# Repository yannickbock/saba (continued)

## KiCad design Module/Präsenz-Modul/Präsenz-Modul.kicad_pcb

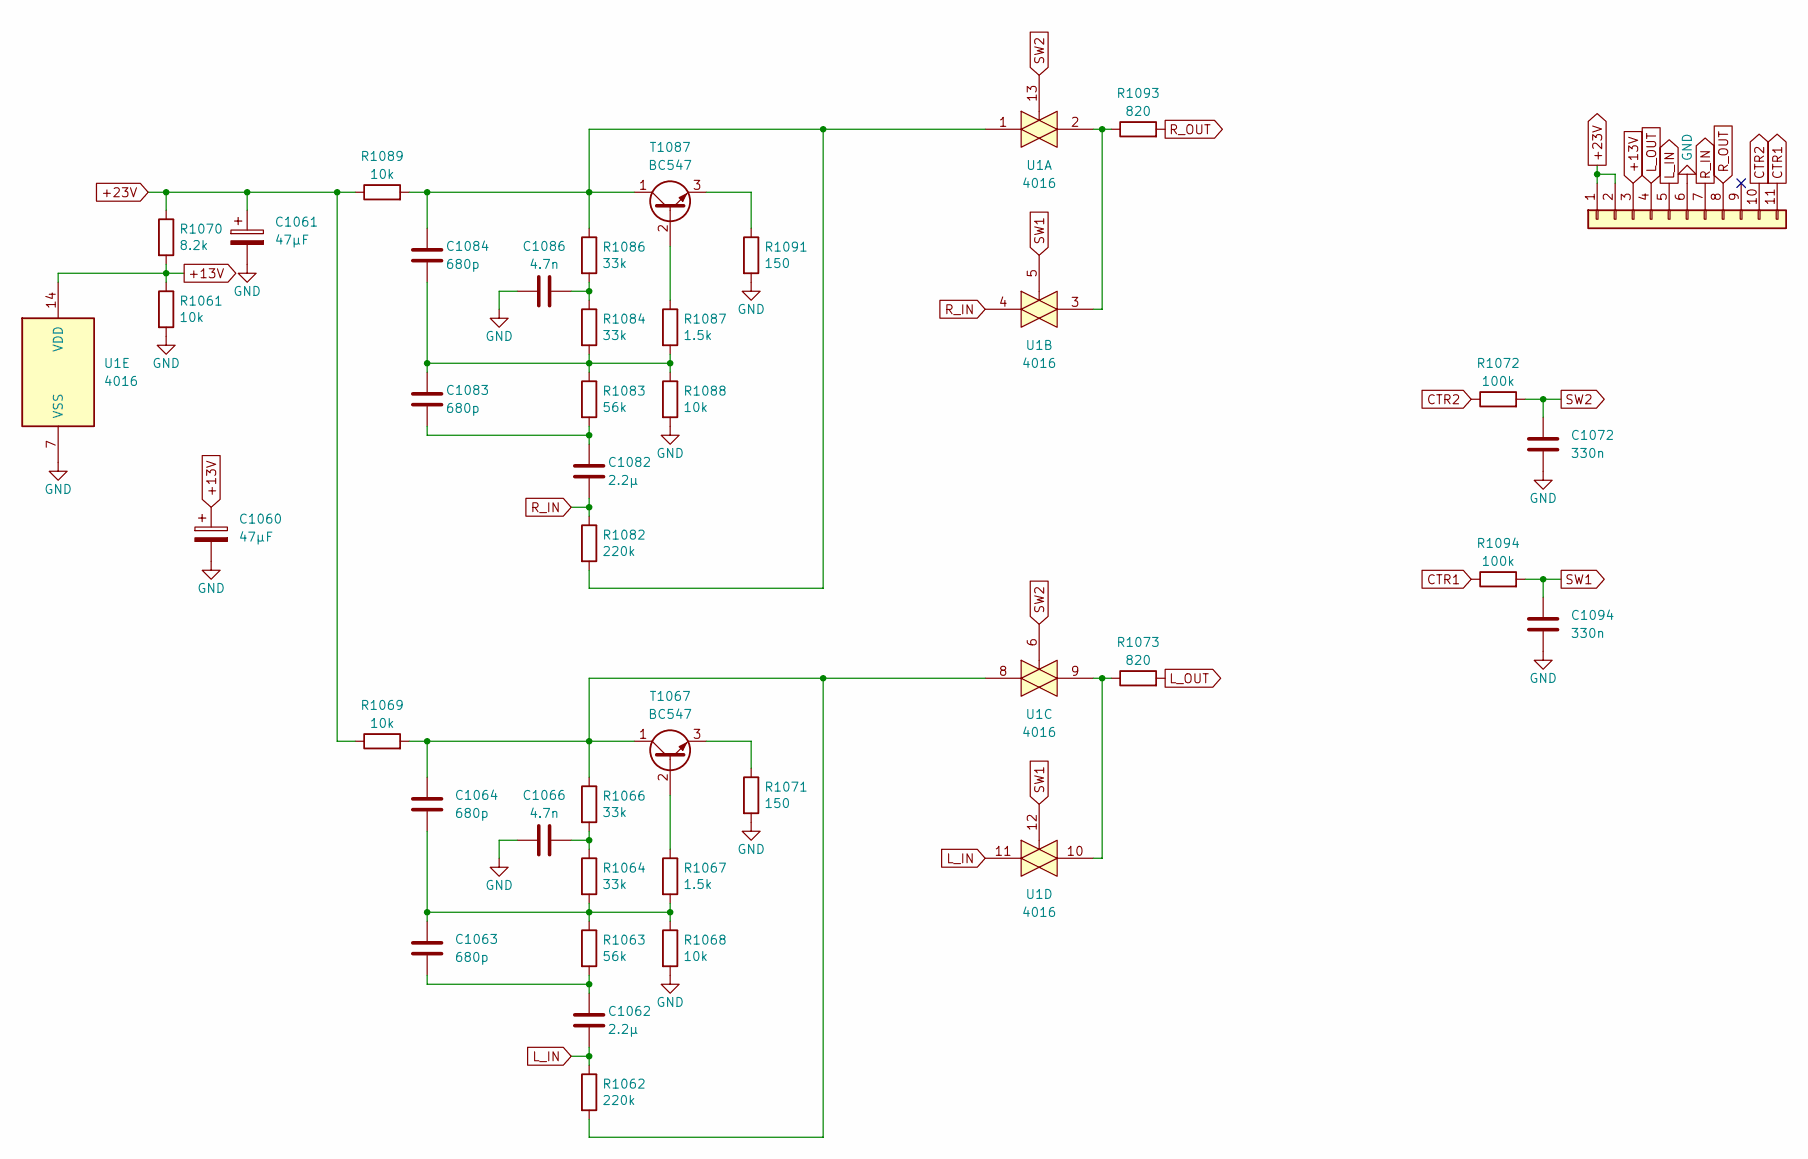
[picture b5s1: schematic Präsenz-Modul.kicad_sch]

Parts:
C1060, C1061: 47µF; CP_Radial_D6.3mm_P2.50mm
C1062, C1082: 2.2µ; C_Rect_L7.2mm_W7.2mm_P5.00mm_FKS2_FKP2_MKS2_MKP2
C1063, C1083: 680p; C_Rect_L10.0mm_W3.0mm_P7.50mm_MKS4
C1064, C1084: 680p; C_RAD_6.5mm_5mm
C1066, C1086: 4.7n; C_Rect_L10.0mm_W3.0mm_P7.50mm_MKS4
C1072, C1094: 330n; C_Rect_L7.2mm_W3.5mm_P5.00mm_FKS2_FKP2_MKS2_MKP2
J1: Conn_01x13; Connector_01x11_5mm
R1061, R1068, R1069, R1088, R1089: 10k; R_Axial_DIN0207_L6.3mm_D2.5mm_P10.16mm_Horizontal
R1062, R1082: 220k; R_Axial_DIN0207_L6.3mm_D2.5mm_P10.16mm_Horizontal
R1063, R1083: 56k; R_Axial_DIN0207_L6.3mm_D2.5mm_P10.16mm_Horizontal
R1064, R1066, R1084, R1086: 33k; R_Axial_DIN0207_L6.3mm_D2.5mm_P10.16mm_Horizontal
R1067, R1087: 1.5k; R_Axial_DIN0207_L6.3mm_D2.5mm_P10.16mm_Horizontal
R1070: 8.2k; R_Axial_DIN0207_L6.3mm_D2.5mm_P10.16mm_Horizontal
R1071, R1091: 150; R_Axial_DIN0207_L6.3mm_D2.5mm_P10.16mm_Horizontal
R1072, R1094: 100k; R_Axial_DIN0207_L6.3mm_D2.5mm_P10.16mm_Horizontal
R1073, R1093: 820; R_Axial_DIN0207_L6.3mm_D2.5mm_P10.16mm_Horizontal
T1067, T1087: BC547; TO-92_Wide
U1: 4016; DIP-14_W7.62mm

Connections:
+13V: C1060.1, J1.3, R1061.1, R1070.2, U1.14 (VDD)
+23V: C1061.1, J1.1, J1.2, R1069.1, R1070.1, R1089.1
CTR1: J1.11, R1094.1
CTR2: J1.10, R1072.1
GND: C1060.2, C1061.2, C1066.1, C1072.2, C1086.1, C1094.2, J1.6, R1061.2, R1068.2, R1071.2, R1088.2, R1091.2, U1.7 (VSS)
L_IN: C1062.2, J1.5, R1062.1, U1.11
L_OUT: J1.4, R1073.2
unnamed: C1062.1, C1063.2, R1063.2
unnamed: C1063.1, C1064.2, R1063.1, R1064.2, R1067.2, R1068.1
unnamed: C1066.2, R1064.1, R1066.2
unnamed: C1082.1, C1083.2, R1083.2
unnamed: C1083.1, C1084.2, R1083.1, R1084.2, R1087.2, R1088.1
unnamed: C1086.2, R1084.1, R1086.2
unnamed: R1073.1, U1.9, U1.10
unnamed: R1093.1, U1.2, U1.3
unnamed: R1067.1, T1067.2 (B)
unnamed: C1064.1, R1062.2, R1066.1, R1069.2, T1067.1 (C), U1.8
unnamed: R1071.1, T1067.3 (E)
unnamed: R1087.1, T1087.2 (B)
unnamed: C1084.1, R1082.2, R1086.1, R1089.2, T1087.1 (C), U1.1
unnamed: R1091.1, T1087.3 (E)
R_IN: C1082.2, J1.7, R1082.1, U1.4
R_OUT: J1.8, R1093.2
SW1: C1094.1, R1094.2, U1.5, U1.12
SW2: C1072.1, R1072.2, U1.6, U1.13

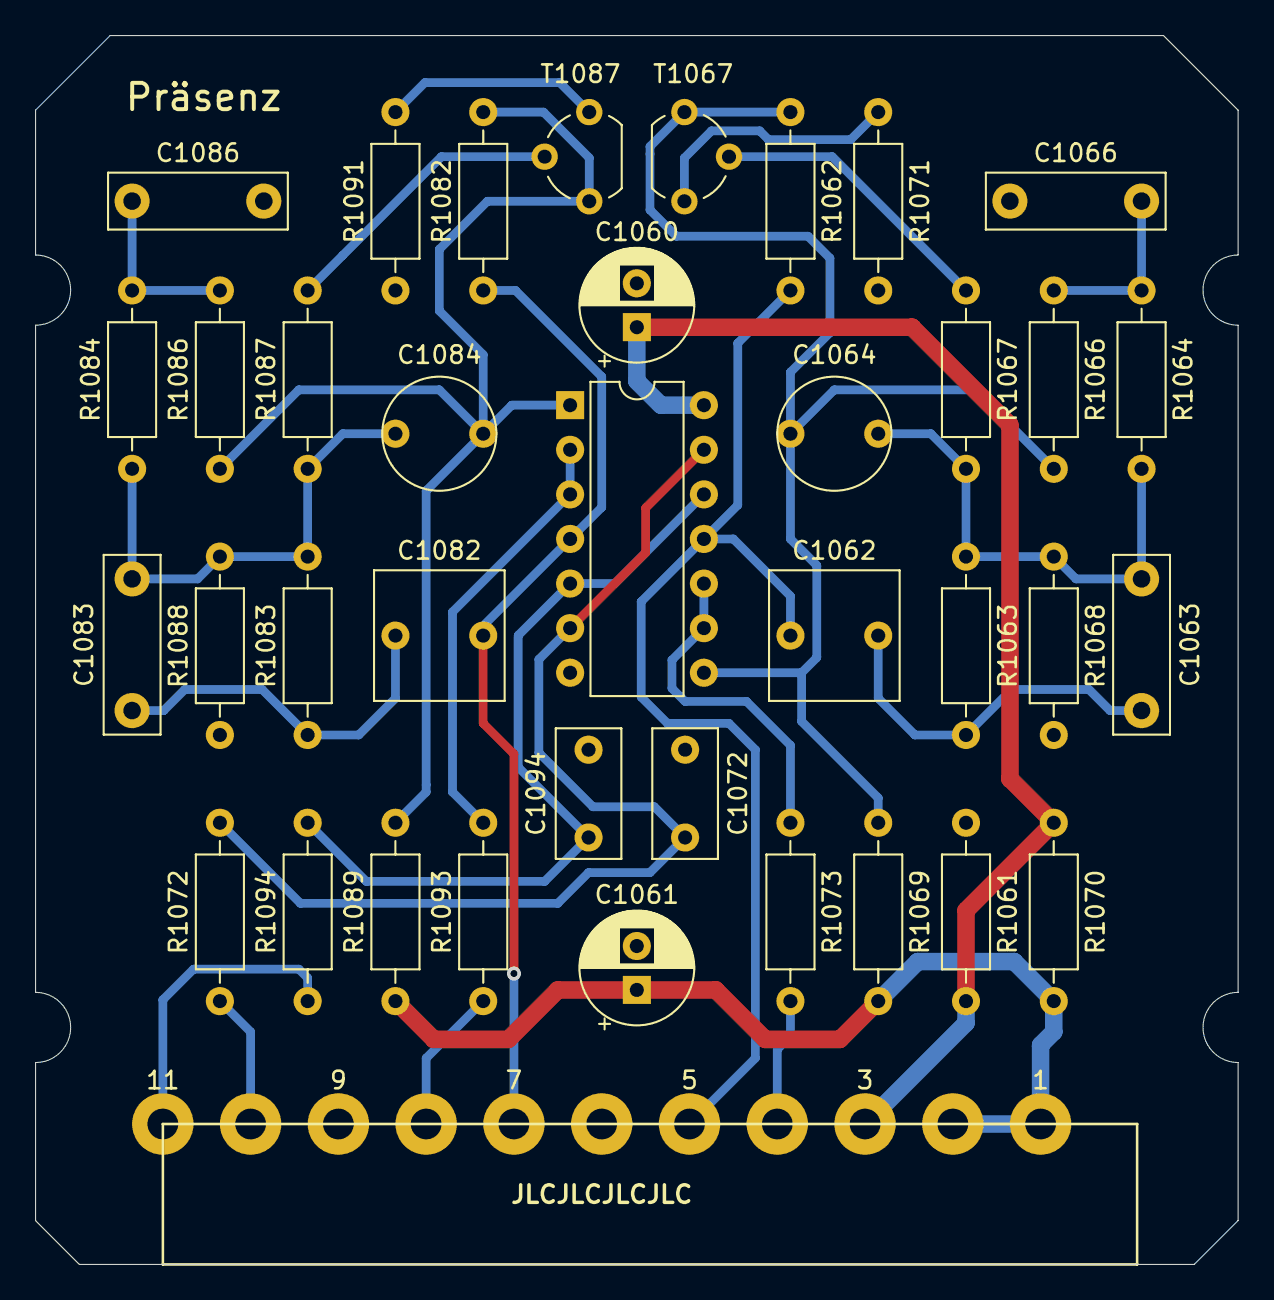
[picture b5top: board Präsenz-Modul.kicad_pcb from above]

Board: 2 copper layers, 68.5 x 70.0 mm, 38 parts (0 on the bottom side), 25 nets.

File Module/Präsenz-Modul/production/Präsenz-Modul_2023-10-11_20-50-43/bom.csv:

Designator,Footprint,Quantity,Value,LCSC Part #
"C1060, C1061",CP_Radial_D6.3mm_P2.50mm,2,47µF,
"C1062, C1082",C_Rect_L7.2mm_W7.2mm_P5.00mm_FKS2_FKP2_MKS2_MKP2,2,2.2µ,
"C1063, C1083",C_Rect_L10.0mm_W3.0mm_P7.50mm_MKS4,2,680p,
"C1064, C1084",C_RAD_6.5mm_5mm,2,680p,
"C1066, C1086",C_Rect_L10.0mm_W3.0mm_P7.50mm_MKS4,2,4.7n,
"C1072, C1094",C_Rect_L7.2mm_W3.5mm_P5.00mm_FKS2_FKP2_MKS2_MKP2,2,330n,
J1,Connector_01x11_5mm,1,Conn_01x13,
"R1061, R1068, R1069, R1088, R1089",R_Axial_DIN0207_L6.3mm_D2.5mm_P10.16mm_Horizontal,5,10k,
"R1062, R1082",R_Axial_DIN0207_L6.3mm_D2.5mm_P10.16mm_Horizontal,2,220k,
"R1063, R1083",R_Axial_DIN0207_L6.3mm_D2.5mm_P10.16mm_Horizontal,2,56k,
"R1064, R1066, R1084, R1086",R_Axial_DIN0207_L6.3mm_D2.5mm_P10.16mm_Horizontal,4,33k,
"R1067, R1087",R_Axial_DIN0207_L6.3mm_D2.5mm_P10.16mm_Horizontal,2,1.5k,
R1070,R_Axial_DIN0207_L6.3mm_D2.5mm_P10.16mm_Horizontal,1,8.2k,
"R1071, R1091",R_Axial_DIN0207_L6.3mm_D2.5mm_P10.16mm_Horizontal,2,150,
"R1072, R1094",R_Axial_DIN0207_L6.3mm_D2.5mm_P10.16mm_Horizontal,2,100k,
"R1073, R1093",R_Axial_DIN0207_L6.3mm_D2.5mm_P10.16mm_Horizontal,2,820,
"T1067, T1087",TO-92_Wide,2,BC550,
U1,DIP-14_W7.62mm,1,CD4016,

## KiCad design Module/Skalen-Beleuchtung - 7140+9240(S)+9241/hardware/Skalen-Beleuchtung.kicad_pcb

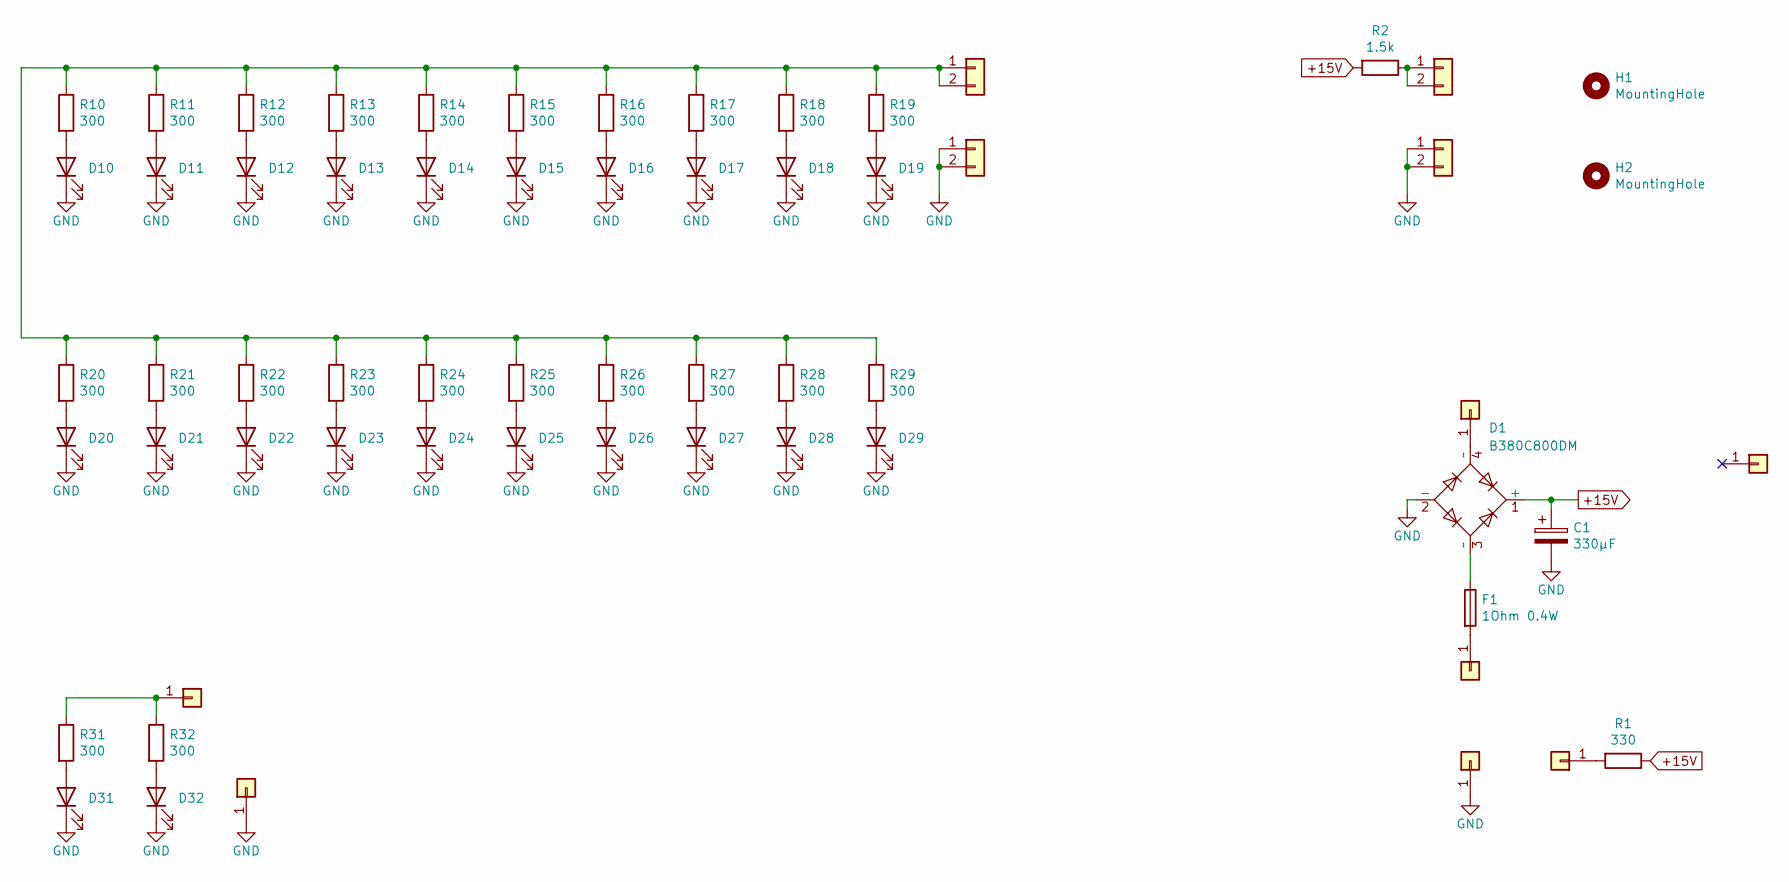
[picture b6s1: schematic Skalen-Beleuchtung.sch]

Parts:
C1: 330µF; CP_Radial_D8.0mm_P3.50mm
D1: B380C800DM; Diode_Bridge_DIP-4_W7.62mm_P5.08mm
D10, D11, D12, D13, D14, D15, D16, D17, D18, D19, D20, D21, D22, D23, D24, D25, D26, D27, D28, D29, D31, D32: LEXTAR-PC35H13-V1; LCSC C317646
F1: 1Ohm 0.4W; R_Axial_DIN0207_L6.3mm_D2.5mm_P10.16mm_Horizontal
H1, H2: MountingHole; MountingHole_3.2mm_M3_DIN965
J1, J2, J3, J4, J9, J10, J11: Conn_01x01; SolderWirePad_single_1mmDrill
J5, J6, J7, J8: Conn_01x02; Pin_Header_Straight_1x02_Pitch2.54mm
R1: 330; R_Axial_DIN0207_L6.3mm_D2.5mm_P10.16mm_Horizontal
R2: 1.5k; R_Axial_DIN0207_L6.3mm_D2.5mm_P10.16mm_Horizontal
R10, R11, R12, R13, R14, R15, R16, R17, R18, R19, R20, R21, R22, R23, R24, R25, R26, R27, R28, R29, R31, R32: 300; R_1206; LCSC C17887

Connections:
+15V: C1.1, D1.1 (+), R1.1, R2.2
GND: C1.2, D1.2 (-), D10.1 (K), D11.1 (K), D12.1 (K), D13.1 (K), D14.1 (K), D15.1 (K), D16.1 (K), D17.1 (K), D18.1 (K), D19.1 (K), D20.1 (K), D21.1 (K), D22.1 (K), D23.1 (K), D24.1 (K), D25.1 (K), D26.1 (K), D27.1 (K), D28.1 (K), D29.1 (K), D31.1 (K), D32.1 (K), J2.1, J6.1, J6.2, J8.1, J8.2, J11.1
unnamed: D1.3 (~~), F1.1
unnamed: D1.4 (~~), J1.1
unnamed: D10.2 (A), R10.2
unnamed: D11.2 (A), R11.2
unnamed: D12.2 (A), R12.2
unnamed: D13.2 (A), R13.2
unnamed: D14.2 (A), R14.2
unnamed: D15.2 (A), R15.2
unnamed: D16.2 (A), R16.2
unnamed: D17.2 (A), R17.2
unnamed: D18.2 (A), R18.2
unnamed: D19.2 (A), R19.2
unnamed: D20.2 (A), R20.2
unnamed: D21.2 (A), R21.2
unnamed: D22.2 (A), R22.2
unnamed: D23.2 (A), R23.2
unnamed: D24.2 (A), R24.2
unnamed: D25.2 (A), R25.2
unnamed: D26.2 (A), R26.2
unnamed: D27.2 (A), R27.2
unnamed: D28.2 (A), R28.2
unnamed: D29.2 (A), R29.2
unnamed: D31.2 (A), R31.2
unnamed: D32.2 (A), R32.2
unnamed: F1.2, J4.1
unnamed: J3.1, R1.2
unnamed: J5.1, J5.2, R2.1
unnamed: J7.1, J7.2, R10.1, R11.1, R12.1, R13.1, R14.1, R15.1, R16.1, R17.1, R18.1, R19.1, R20.1, R21.1, R22.1, R23.1, R24.1, R25.1, R26.1, R27.1, R28.1, R29.1
unnamed: J10.1, R31.1, R32.1

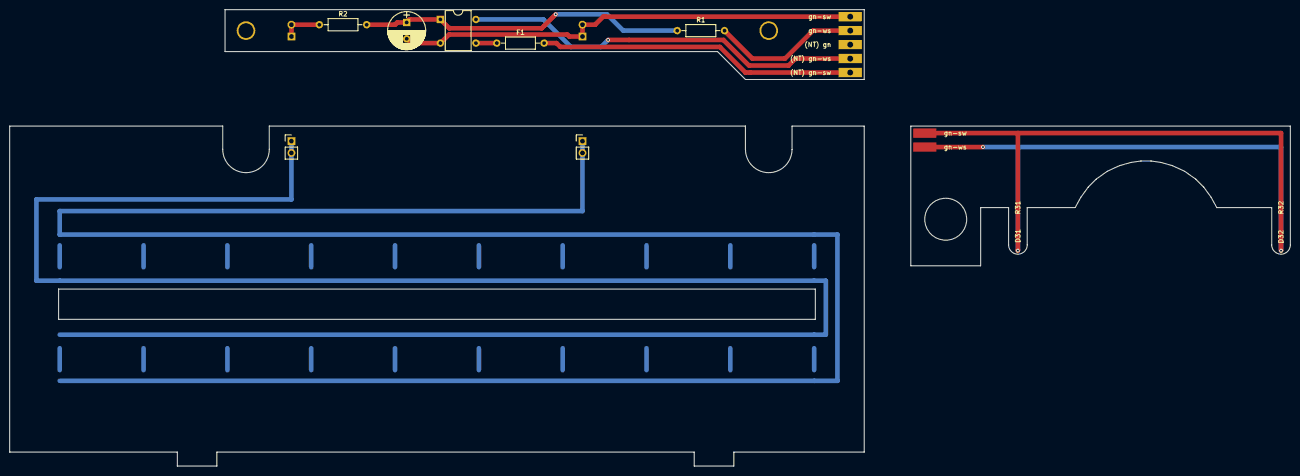
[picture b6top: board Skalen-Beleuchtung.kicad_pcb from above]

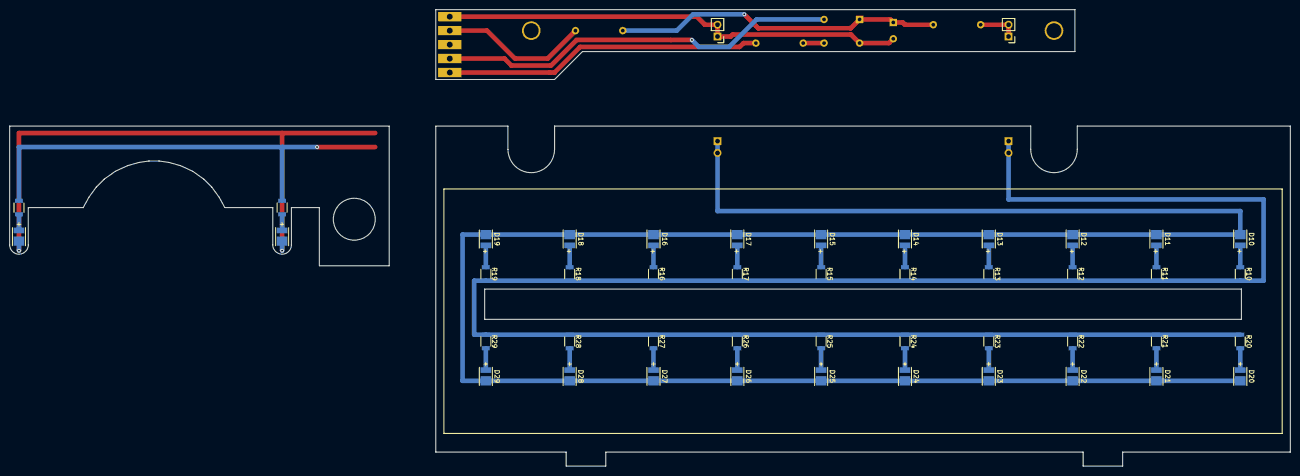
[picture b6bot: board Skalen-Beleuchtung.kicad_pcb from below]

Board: 2 copper layers, 275.0 x 98.0 mm, 62 parts (46 on the bottom side), 31 nets.

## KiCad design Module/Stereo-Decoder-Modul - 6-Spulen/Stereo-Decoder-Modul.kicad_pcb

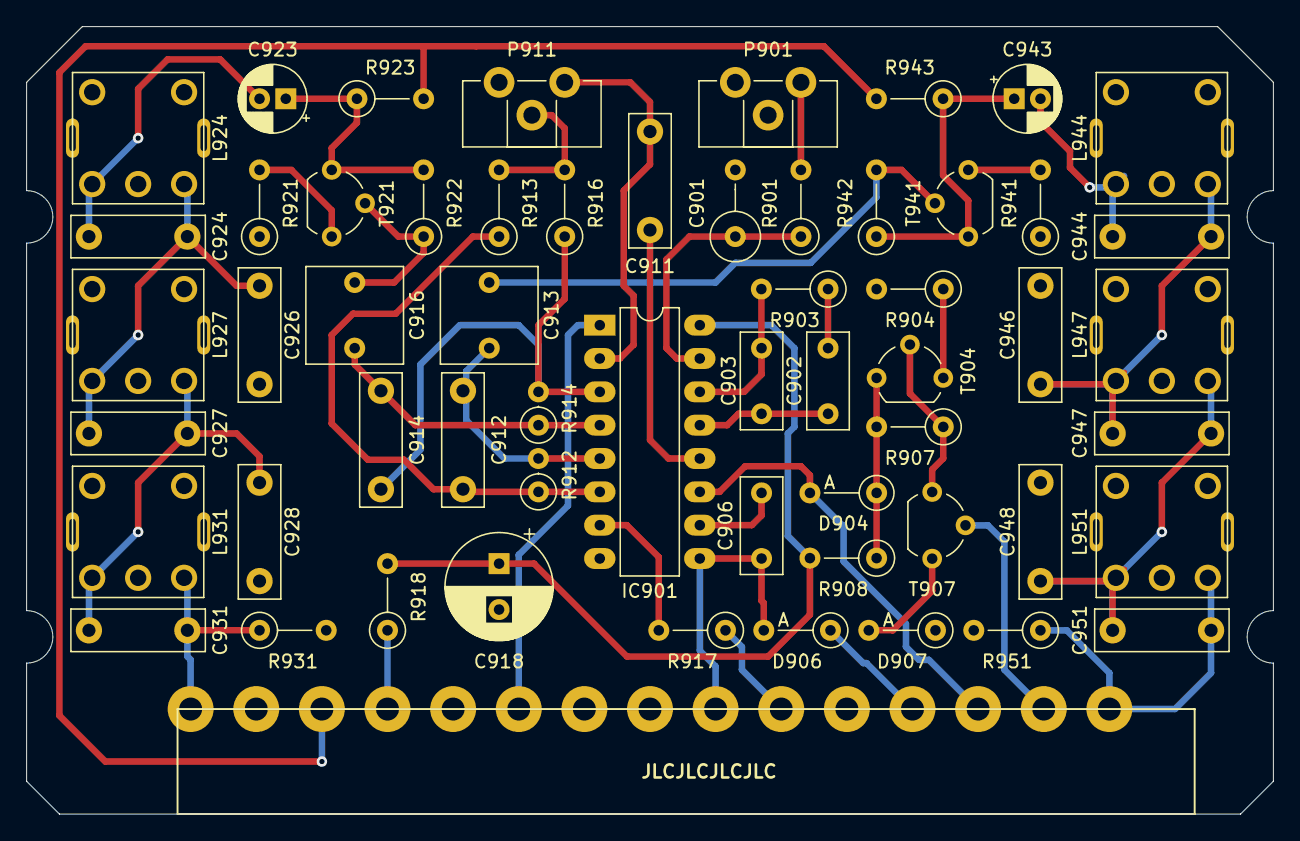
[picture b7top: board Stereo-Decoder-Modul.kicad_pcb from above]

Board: 2 copper layers, 95.0 x 60.0 mm, 58 parts (0 on the bottom side), 41 nets.

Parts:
C901: C; R_Axial_DIN0411_L9.9mm_D3.6mm_P5.08mm_Vertical
C902, C903, C906: C; C_Rect_L7.2mm_W3.0mm_P5.00mm_FKS2_FKP2_MKS2_MKP2
C911, C912, C914, C924, C926, C927, C928, C931, C944, C946, C947, C948, C951: C; C_Rect_L10.0mm_W3.0mm_P7.50mm_MKS4
C913, C916: 4.7µF; C_Rect_L7.2mm_W7.2mm_P5.00mm_FKS2_FKP2_MKS2_MKP2
C918: 220µF; CP_Radial_D8.0mm_P3.50mm
C923, C943: 22µF; CP_Radial_D5.0mm_P2.00mm
D904, D906, D907: D; D_DO-35_SOD27_P5.08mm_Vertical_AnodeUp
IC901: TCA4500A; DIP-16_W7.62mm_LongPads
J1: Conn_01x15; Connector_01x15_5mm
L924, L927, L931, L944, L947, L951: L_Trim; Inductor_Adjustable
P901: 5k; Potentiometer_Piher_PT-10-H01_Horizontal
P911: 10k; Potentiometer_Piher_PT-10-H01_Horizontal
R901, R903, R904, R907, R908, R913, R916, R917, R918, R921, R922, R923, R931, R941, R942, R943, R951: R; R_Axial_DIN0207_L6.3mm_D2.5mm_P5.08mm_Vertical
R912, R914: R; R_Axial_DIN0207_L6.3mm_D2.5mm_P2.54mm_Vertical
T904, T907, T921, T941: BC547; TO-92_Wide

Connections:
+30V: J1.13, R923.2, R943.2
GND: C901.2, C918.2, C926.2, C928.2, C946.2, C948.2, D907.1 (K), IC901.8, J1.5, J1.9, J1.11, J1.14, L924.6 (GND), L927.6 (GND), L931.6 (GND), L944.6 (GND), L947.6 (GND), L951.6 (GND), P901.2, P901.3, P911.3, R904.2, R921.1, R931.2, R941.1, R951.2
unnamed: C901.1, IC901.15, R901.1
unnamed: C902.1, R903.1
unnamed: C906.2, IC901.10
unnamed: C912.2, IC901.6, R912.1, R913.1
unnamed: C912.1, C913.1, IC901.5, R912.2
unnamed: C913.2, R942.2, T941.2 (B)
unnamed: C914.1, IC901.3, R914.2, R916.1
unnamed: C914.2, C916.1, IC901.4, R914.1
unnamed: C916.2, R922.1, T921.2 (B)
unnamed: C918.1, IC901.16, R908.2, R918.2
unnamed: C923.1, R922.2, R923.1, T921.1 (C)
unnamed: C923.2, C924.1, L924.1
unnamed: C924.2, C926.1, C927.1, L924.2, L927.1
unnamed: C943.1, R942.1, R943.1, T941.1 (C)
unnamed: C943.2, C944.1, L944.1
unnamed: D904.1 (K), R907.2, R908.1, T904.1 (C)
unnamed: D907.2 (A), T907.3 (E)
unnamed: C911.2, IC901.2, P911.1
unnamed: IC901.7, R917.2
unnamed: C911.1, IC901.12
unnamed: C902.2, C903.1, IC901.13
unnamed: C903.2, IC901.14, R903.2
unnamed: C927.2, C928.1, C931.1, L927.2, L931.1
unnamed: C944.2, C946.1, C947.1, L944.2, L947.1
unnamed: C947.2, C948.1, C951.1, L947.2, L951.1
unnamed: P901.1, R901.2
unnamed: R904.1, T904.3 (E)
unnamed: R907.1, T904.2 (B), T907.1 (C)
unnamed: P911.2, R913.2, R916.2
unnamed: R921.2, T921.3 (E)
unnamed: R941.2, T941.3 (E)
P1: C951.2, J1.1, L951.2, R951.1
P2: J1.2, T907.2 (B)
P3: D904.2 (A), IC901.11, J1.3
P4: D906.1 (K), J1.4
P6: J1.6, R917.1
P7: C906.1, D906.2 (A), IC901.9, J1.7
P12: J1.12, R918.1
P15: C931.2, J1.15, L931.2, R931.1
